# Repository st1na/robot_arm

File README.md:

# robot_arm
READ Doc.pdf for more info. Language Bulgarian.

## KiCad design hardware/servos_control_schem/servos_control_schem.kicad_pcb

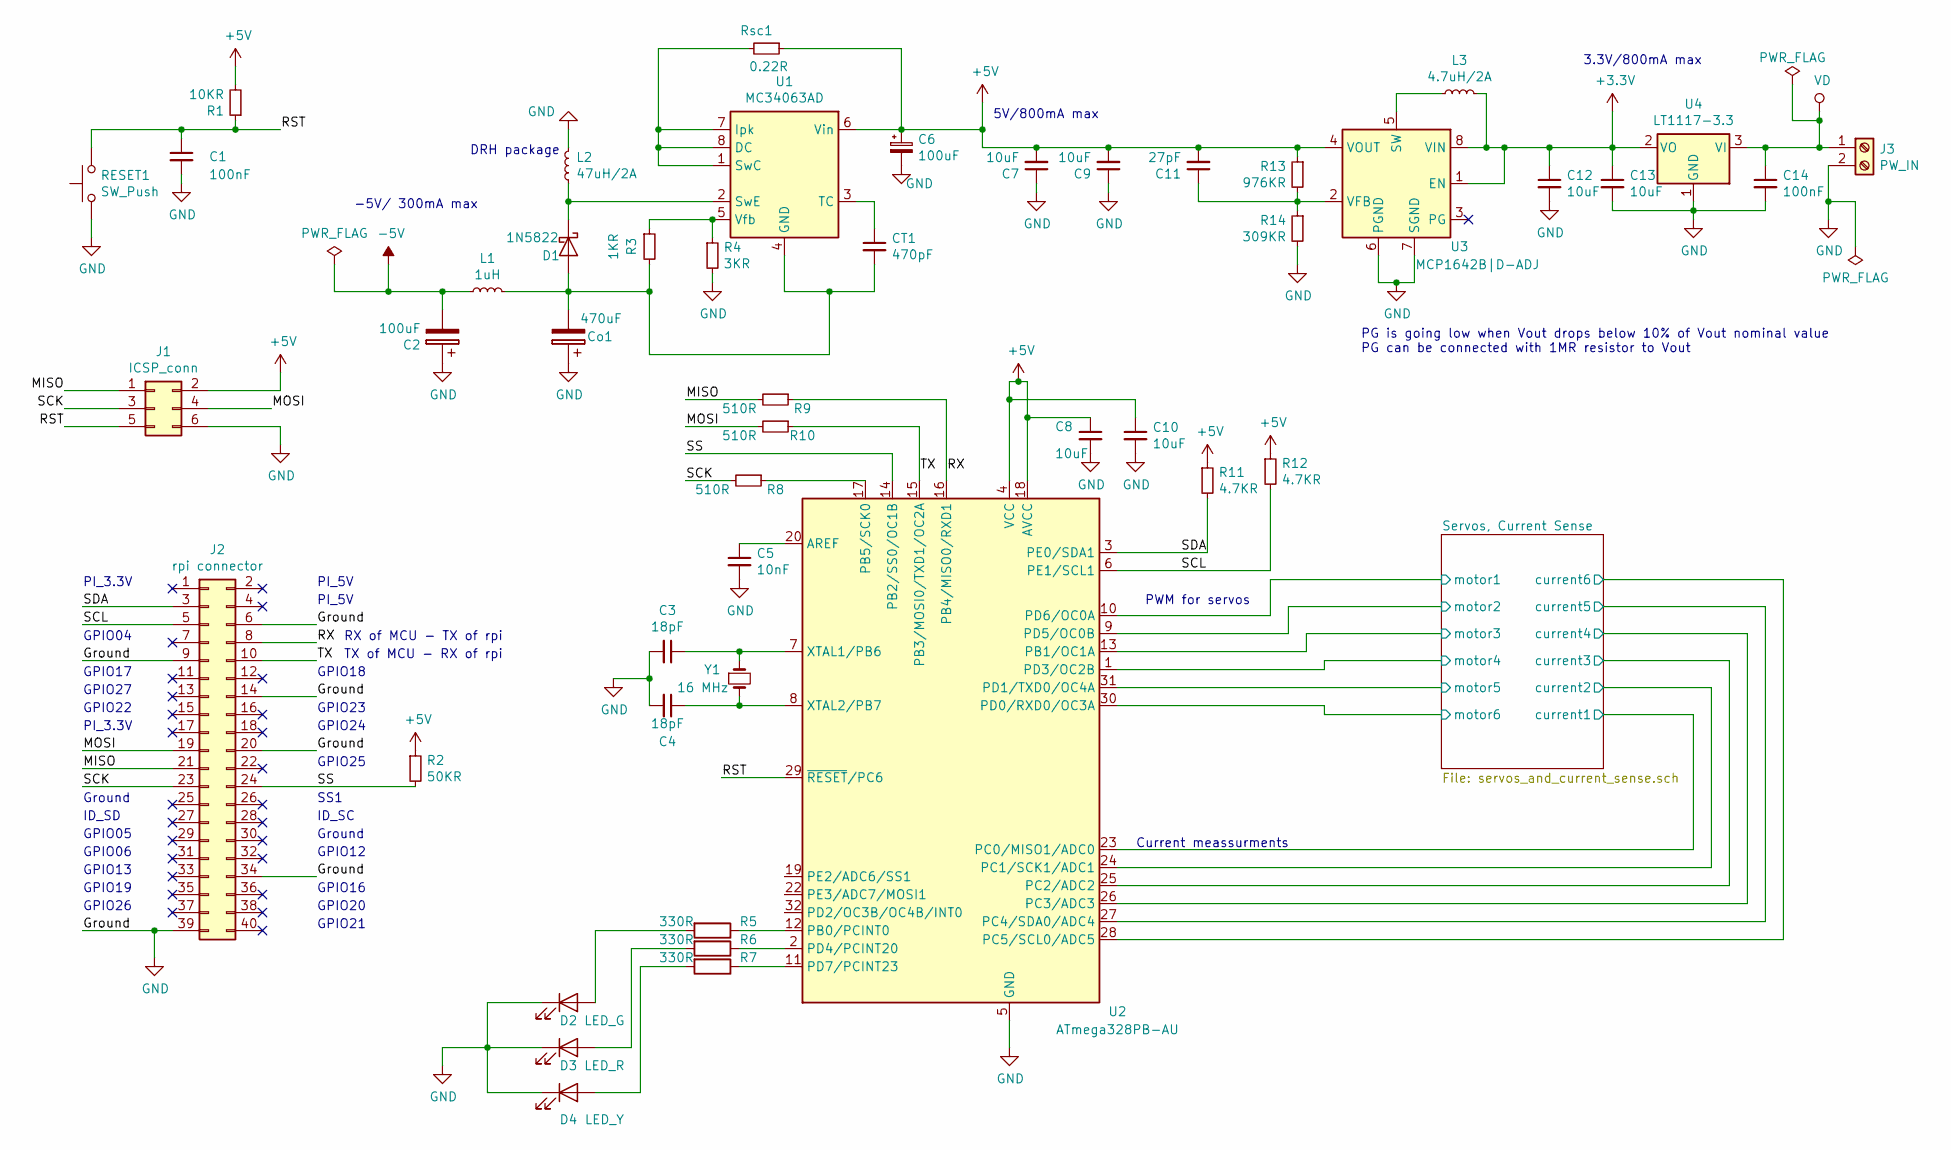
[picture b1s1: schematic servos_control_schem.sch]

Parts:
C1, C14: 100nF; C_0805_2012Metric_Pad1.15x1.40mm_HandSolder
C2, C6: 100uF; CP_Elec_6.3x5.4
C3, C4: 18pF; C_0805_2012Metric_Pad1.15x1.40mm_HandSolder
C5: 10nF; C_0805_2012Metric_Pad1.15x1.40mm_HandSolder
C7, C8, C9, C10, C12, C13: 10uF; C_0805_2012Metric_Pad1.15x1.40mm_HandSolder
C11: 27pF; C_0805_2012Metric_Pad1.15x1.40mm_HandSolder
CT1: 470pF; C_0805_2012Metric_Pad1.15x1.40mm_HandSolder
Co1: 470uF; CP_Elec_6.3x7.7
D1: 1N5822; D_SMC
D2: LED_G; LED_1206_3216Metric_Pad1.42x1.75mm_HandSolder
D3: LED_R; LED_1206_3216Metric_Pad1.42x1.75mm_HandSolder
D4: LED_Y; LED_1206_3216Metric_Pad1.42x1.75mm_HandSolder
J1: ICSP_conn; IDC-Header_2x03_P2.54mm_Vertical
J2: rpi connector; IDC-Header_2x20_P2.54mm_Vertical
J3: PW_IN; TerminalBlock_bornier-2_P5.08mm
L1: 1uH; L_1210_3225Metric_Pad1.42x2.65mm_HandSolder
L2: 47uH/2A; L_12x12mm_H6mm
L3: 4.7uH/2A; L_7.3x7.3_H3.5
R1: 10KR; R_0805_2012Metric_Pad1.15x1.40mm_HandSolder
R2: 50KR; R_0805_2012Metric_Pad1.15x1.40mm_HandSolder
R3: 1KR; R_0805_2012Metric_Pad1.15x1.40mm_HandSolder
R4: 3KR; R_0805_2012Metric_Pad1.15x1.40mm_HandSolder
R5, R6, R7: 330R; R_0805_2012Metric_Pad1.15x1.40mm_HandSolder
R8, R9, R10: 510R; R_0805_2012Metric_Pad1.15x1.40mm_HandSolder
R11, R12: 4.7KR; R_0805_2012Metric_Pad1.15x1.40mm_HandSolder
R13: 976KR; R_0805_2012Metric_Pad1.15x1.40mm_HandSolder
R14: 309KR; R_0805_2012Metric_Pad1.15x1.40mm_HandSolder
RESET1: SW_Push; SW_SPST_FSMSM
Rsc1: 0.22R; R_0805_2012Metric_Pad1.15x1.40mm_HandSolder
U1: MC34063AD; SOIC-8_3.9x4.9mm_P1.27mm
U2: ATmega328PB-AU; TQFP-32_7x7mm_P0.8mm
U3: MCP1642B|D-ADJ; MSOP-8_3x3mm_P0.65mm
U4: LT1117-3.3; SOT-223
Y1: 16 MHz; Crystal_SMD_HC49-SD

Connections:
+3V3: C12.1, C13.1, L3.1, U3.1 (EN), U3.8 (VIN), U4.2 (VO)
+5V: C6.1, C7.2, C8.1, C9.2, C10.1, C11.2, J1.2, R1.2, R2.1, R11.1, R12.1, R13.1, Rsc1.1, U1.6 (Vin), U2.4 (VCC), U2.18 (AVCC), U3.4 (VOUT); also elsewhere on the board
-5V: C2.2, L1.1; also elsewhere on the board
/MISO: J1.1, J2.21, R9.2
/MOSI: J1.4, J2.19, R10.2
/RST: C1.1, J1.5, R1.1, RESET1.2, U2.29 (~RESET~/PC6)
/RX: J2.8, R9.1, U2.16 (PB4/MISO0/RXD1)
/SCK: J1.3, J2.23, R8.2
/SCL: J2.5, R12.2, U2.6 (PE1/SCL1)
/SDA: J2.3, R11.2, U2.3 (PE0/SDA1)
/SS: J2.24, R2.2, U2.14 (PB2/SS0/OC1B)
/Servos, Current Sense/current1: U2.23 (PC0/MISO1/ADC0); also elsewhere on the board
/Servos, Current Sense/current2: U2.24 (PC1/SCK1/ADC1); also elsewhere on the board
/Servos, Current Sense/current3: U2.25 (PC2/ADC2); also elsewhere on the board
/Servos, Current Sense/current4: U2.26 (PC3/ADC3); also elsewhere on the board
/Servos, Current Sense/current5: U2.27 (PC4/SDA0/ADC4); also elsewhere on the board
/Servos, Current Sense/current6: U2.28 (PC5/SCL0/ADC5); also elsewhere on the board
/Servos, Current Sense/motor1: U2.10 (PD6/OC0A); also elsewhere on the board
/Servos, Current Sense/motor2: U2.9 (PD5/OC0B); also elsewhere on the board
/Servos, Current Sense/motor3: U2.13 (PB1/OC1A); also elsewhere on the board
/Servos, Current Sense/motor4: U2.1 (PD3/OC2B); also elsewhere on the board
/Servos, Current Sense/motor5: U2.31 (PD1/TXD0/OC4A); also elsewhere on the board
/Servos, Current Sense/motor6: U2.30 (PD0/RXD0/OC3A); also elsewhere on the board
/TX: J2.10, R10.1, U2.15 (PB3/MOSI0/TXD1/OC2A)
GND: C1.2, C2.1, C3.2, C4.2, C5.2, C6.2, C7.1, C8.2, C9.1, C10.2, C12.2, C13.2, C14.2, Co1.1, D2.1 (K), D3.1 (K), D4.1 (K), J1.6, J2.6, J2.9, J2.14, J2.20, J2.34, J2.39, J3.2, L2.2, R4.2, R14.2, RESET1.1, U2.5 (GND), U2.21 (GND), U3.6 (PGND), U3.7 (SGND), U4.1 (GND); also elsewhere on the board
unnamed: C3.1, U2.7 (XTAL1/PB6), Y1.1
unnamed: C4.1, U2.8 (XTAL2/PB7), Y1.2
unnamed: C5.1, U2.20 (AREF)
unnamed: C11.1, R13.2, R14.1, U3.2 (VFB)
unnamed: CT1.1, U1.3 (TC)
unnamed: CT1.2, Co1.2, D1.2 (A), L1.2, R3.2, U1.4 (GND)
unnamed: D1.1 (K), L2.1, U1.2 (SwE)
unnamed: D2.2 (A), R5.2
unnamed: D3.2 (A), R6.2
unnamed: D4.2 (A), R7.2
unnamed: L3.2, U3.5 (SW)
unnamed: R3.1, R4.1, U1.5 (Vfb)
unnamed: R5.1, U2.12 (PB0/PCINT0)
unnamed: R6.1, U2.2 (PD4/PCINT20)
unnamed: R7.1, U2.11 (PD7/PCINT23)
unnamed: R8.1, U2.17 (PB5/SCK0)
unnamed: Rsc1.2, U1.1 (SwC), U1.7 (Ipk), U1.8 (DC)
VD: C14.1, J3.1, U4.3 (VI); also elsewhere on the board

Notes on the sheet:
PWM for servos
Current meassurments
5V/800mA max
3.3V/800mA max
RX of MCU - TX of rpi
TX of MCU - RX of rpi
PG is going low when Vout drops below 10% of Vout nominal value PG can be connected with 1MR resistor to Vout
-5V/ 300mA max
DRH package
PI_3.3V
GPIO04
GPIO17
GPIO27
GPIO22
Ground
ID_SD
GPIO05
GPIO06
GPIO13
GPIO19
GPIO26
PI_5V
GPIO18
GPIO23
GPIO24
GPIO25
SS1
ID_SC
GPIO12
GPIO16
GPIO20
GPIO21

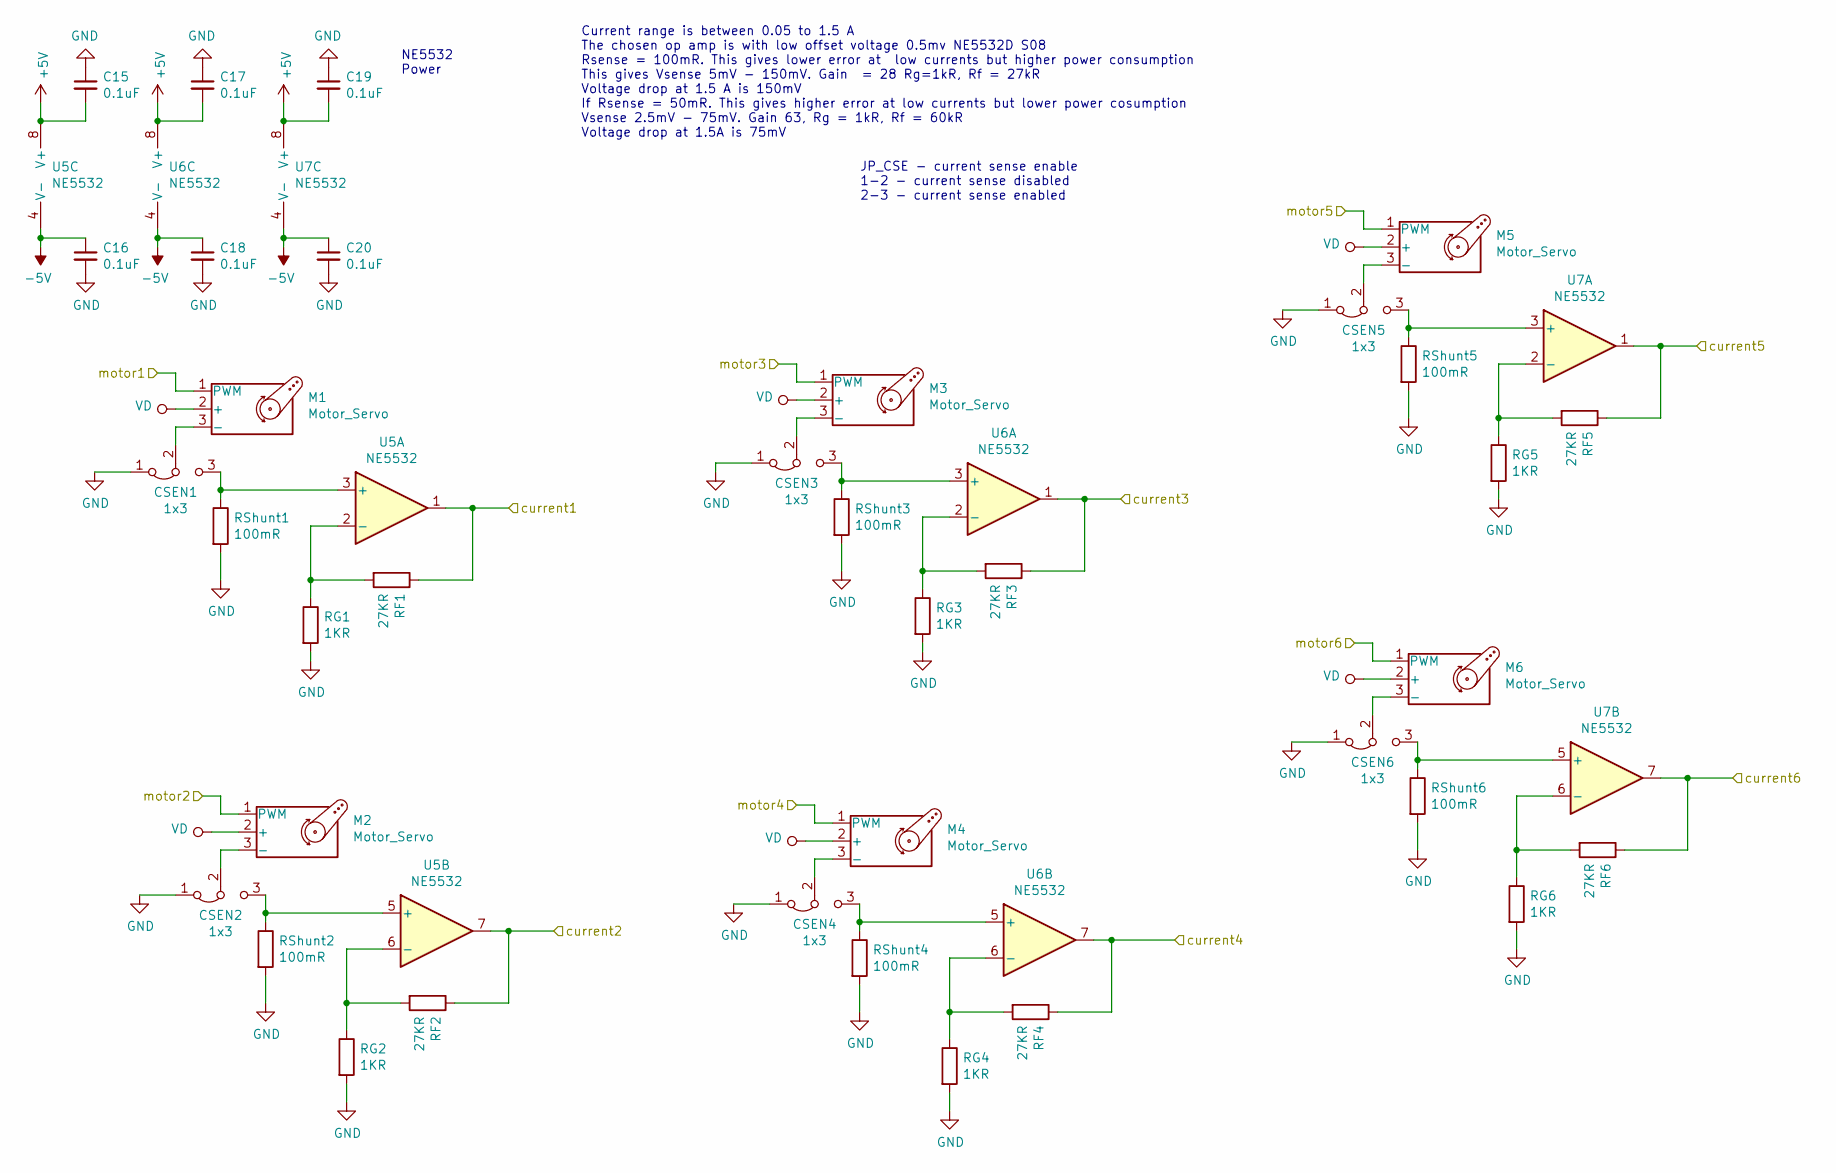
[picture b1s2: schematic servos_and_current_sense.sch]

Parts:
C15, C16, C17, C18, C19, C20: 0.1uF; C_0805_2012Metric_Pad1.15x1.40mm_HandSolder
CSEN1, CSEN2, CSEN3, CSEN4, CSEN5, CSEN6: 1x3; PinHeader_1x03_P2.54mm_Vertical
M1, M2, M3, M4, M5, M6: Motor_Servo; PinHeader_1x03_P2.54mm_Vertical
RF1, RF2, RF3, RF4, RF5, RF6: 27KR; R_0805_2012Metric_Pad1.15x1.40mm_HandSolder
RG1, RG2, RG3, RG4, RG5, RG6: 1KR; R_0805_2012Metric_Pad1.15x1.40mm_HandSolder
RShunt1, RShunt2, RShunt3, RShunt4, RShunt5, RShunt6: 100mR; R_2512_6332Metric_Pad1.52x3.35mm_HandSolder
U5, U6, U7: NE5532; SOIC-8_3.9x4.9mm_P1.27mm

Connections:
+5V: C15.2, C17.2, C19.2, U5.8 (V+), U6.8 (V+), U7.8 (V+); also elsewhere on the board
-5V: C16.1, C18.1, C20.1, U5.4 (V-), U6.4 (V-), U7.4 (V-); also elsewhere on the board
/Servos, Current Sense/current1: RF1.1, U5.1; also elsewhere on the board
/Servos, Current Sense/current2: RF2.1, U5.7; also elsewhere on the board
/Servos, Current Sense/current3: RF3.1, U6.1; also elsewhere on the board
/Servos, Current Sense/current4: RF4.1, U6.7; also elsewhere on the board
/Servos, Current Sense/current5: RF5.1, U7.1; also elsewhere on the board
/Servos, Current Sense/current6: RF6.1, U7.7; also elsewhere on the board
/Servos, Current Sense/motor1: M1.1 (PWM); also elsewhere on the board
/Servos, Current Sense/motor2: M2.1 (PWM); also elsewhere on the board
/Servos, Current Sense/motor3: M3.1 (PWM); also elsewhere on the board
/Servos, Current Sense/motor4: M4.1 (PWM); also elsewhere on the board
/Servos, Current Sense/motor5: M5.1 (PWM); also elsewhere on the board
/Servos, Current Sense/motor6: M6.1 (PWM); also elsewhere on the board
GND: C15.1, C16.2, C17.1, C18.2, C19.1, C20.2, CSEN1.1 (A), CSEN2.1 (A), CSEN3.1 (A), CSEN4.1 (A), CSEN5.1 (A), CSEN6.1 (A), RG1.2, RG2.2, RG3.2, RG4.2, RG5.2, RG6.2, RShunt1.2, RShunt2.2, RShunt3.2, RShunt4.2, RShunt5.2, RShunt6.2; also elsewhere on the board
unnamed: CSEN1.2 (C), M1.3 (-)
unnamed: CSEN1.3 (B), RShunt1.1, U5.3 (+)
unnamed: CSEN2.2 (C), M2.3 (-)
unnamed: CSEN2.3 (B), RShunt2.1, U5.5 (+)
unnamed: CSEN3.2 (C), M3.3 (-)
unnamed: CSEN3.3 (B), RShunt3.1, U6.3 (+)
unnamed: CSEN4.2 (C), M4.3 (-)
unnamed: CSEN4.3 (B), RShunt4.1, U6.5 (+)
unnamed: CSEN5.2 (C), M5.3 (-)
unnamed: CSEN5.3 (B), RShunt5.1, U7.3 (+)
unnamed: CSEN6.2 (C), M6.3 (-)
unnamed: CSEN6.3 (B), RShunt6.1, U7.5 (+)
unnamed: RF1.2, RG1.1, U5.2 (-)
unnamed: RF2.2, RG2.1, U5.6 (-)
unnamed: RF3.2, RG3.1, U6.2 (-)
unnamed: RF4.2, RG4.1, U6.6 (-)
unnamed: RF5.2, RG5.1, U7.2 (-)
unnamed: RF6.2, RG6.1, U7.6 (-)
VD: M1.2 (+), M2.2 (+), M3.2 (+), M4.2 (+), M5.2 (+), M6.2 (+); also elsewhere on the board

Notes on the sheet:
NE5532 Power
Current range is between 0.05 to 1.5 A The chosen op amp is with low offset voltage 0.5mv NE5532D S08 Rsense = 100mR. This gives lower error at low currents but higher power consumption This gives Vsense 5mV - 150mV. Gain = 28 Rg=1kR, Rf = 27kR Voltage drop at 1.5 A is 150mV If Rsense = 50mR. This 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
JP_CSE - current sense enable 1-2 - current sense disabled 2-3 - current sense enabled

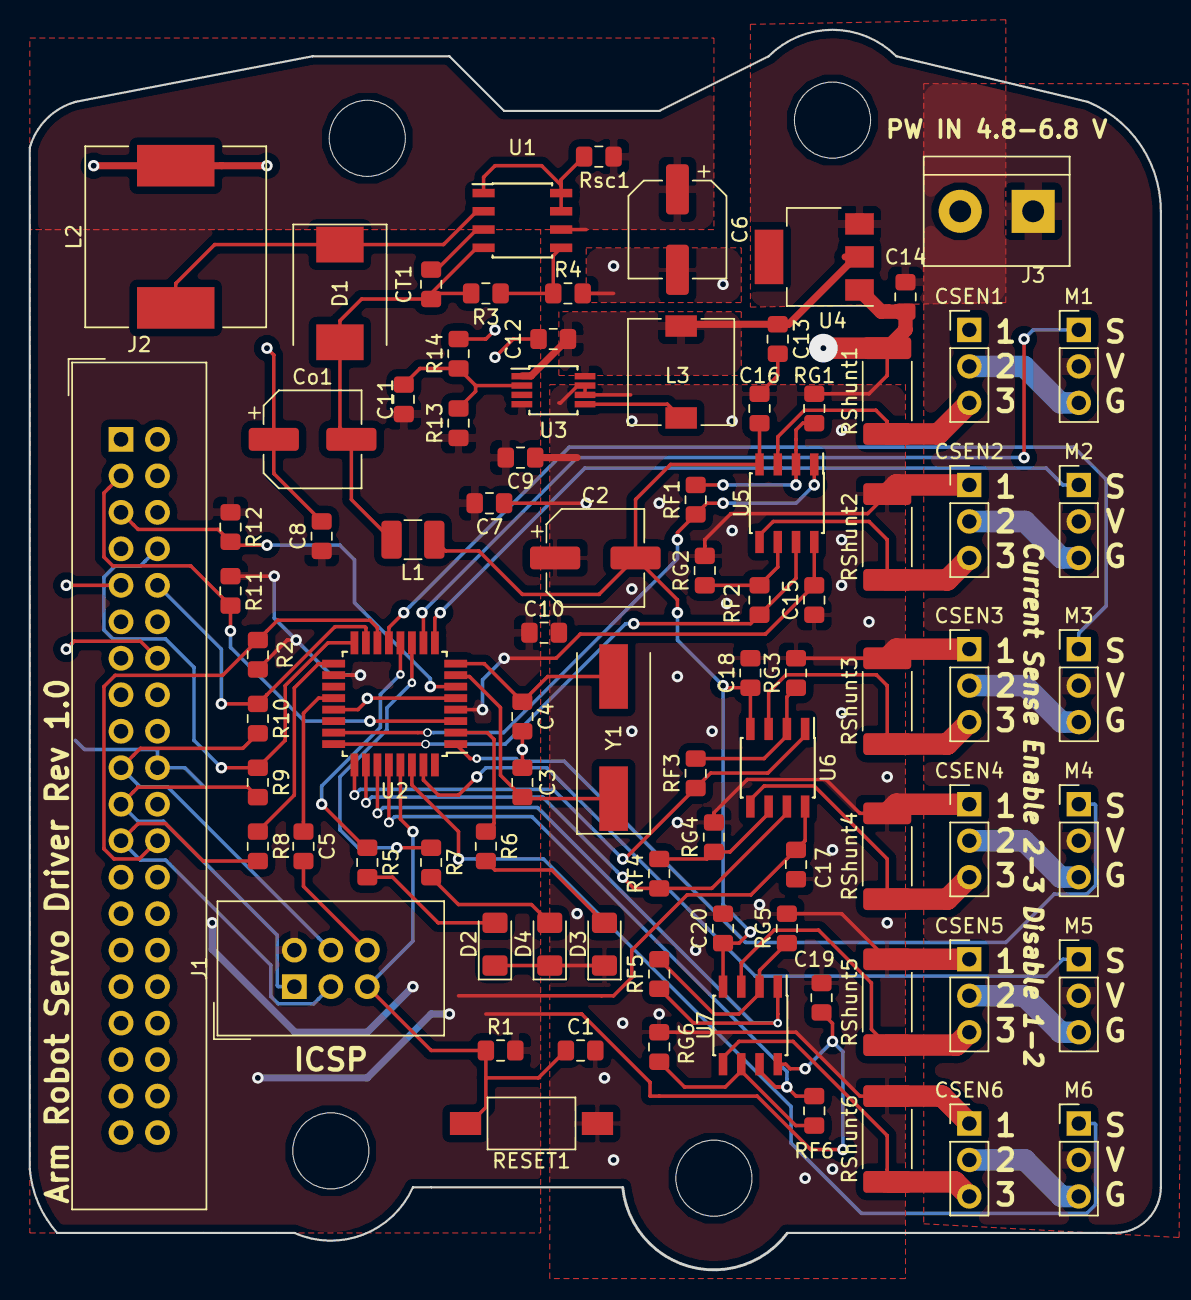
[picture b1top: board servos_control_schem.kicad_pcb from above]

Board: 2 copper layers, 78.7 x 86.3 mm, 86 parts (0 on the bottom side), 61 nets.

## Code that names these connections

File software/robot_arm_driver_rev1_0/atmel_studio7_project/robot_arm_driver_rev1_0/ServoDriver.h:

/*
 * ServoDriver.h
 *
 * Created: 06/04/2019 17:50:24
 *  Author: st1na
 */ 


#ifndef SERVODRIVER_H_
#define SERVODRIVER_H_

#define F_CPU 16000000
#define __DELAY_BACKWARD_COMPATIBLE__

#include <avr/io.h>
#include <stdbool.h>
#include <avr/interrupt.h>
#include <stdint.h>
#include <util/delay.h>


#define DDR_MOTOR DDRD
#define DDR_MOTOR3 DDRB
#define PORT_MOTOR PORTD
#define MOTOR1 PD6
#define MOTOR2 PD5
#define MOTOR3 PB1
#define MOTOR4 PD3
#define MOTOR5 PD1
#define MOTOR6 PD0

#define NUM_JOINTS		6
#define ARM_JOINTS		5
#define GRIPPER_JOINT	6

volatile double servo1_us;
volatile double servo2_us;
volatile double servo4_us;
#define servo3_us OCR1A
#define servo5_us OCR4A
#define servo6_us OCR3A

typedef struct delay{
	volatile double min_delay ;
	volatile double mid_delay ;
	volatile double max_delay ;
	volatile uint8_t min_delay_motor;
	volatile uint8_t mid_delay_motor;
	volatile uint8_t max_delay_motor;
		
} delay ;

delay servo_delay;

void delay_determine();
void initPWM();
void softwarePWMServo(double motor1_us, double motor2_us, double motor4_us);
void setServoAngles(uint8_t* angles);
void anglesToMiliSec(uint8_t* angles, uint16_t* angles_ms);

#endif /* SERVODRIVER_H_ */

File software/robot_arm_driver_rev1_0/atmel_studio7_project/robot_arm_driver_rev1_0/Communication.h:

/*
 * Communication.h
 *
 * Created: 05/04/2019 14:09:56
 *  Author: st1na
 */ 


#ifndef COMMUNICATION_H_
#define COMMUNICATION_H_

// ----------------- Includes ----------------
#include <avr/io.h>
#include <stdbool.h>
#include <avr/interrupt.h>
#include <stdint.h>

// ----------------- Defines ------------------
#define LAST_JOINT_SEND 100
#define NUM_JOINTS		6
#define ARM_JOINTS		5
#define GRIPPER_JOINT	6

#define DDR_SPI DDRB
#define MISO PB4
#define MOSI PB3
#define SS	PB2
#define SCK PB5

// Received joint are in range [-90,+90]
// Last byte hold END_OF_TRANSMISSION 
volatile int8_t joints_buffer[7];
// Mapped joints to [0; 180] 
volatile uint8_t u_joints_buffer[6];
volatile uint8_t joint_number;
volatile bool process_joints;

// ----------------- Prototypes -----------------

void initSPISlave(void);
void mapJointsFromSPI(void);
bool checkSPI_status(void);
void getJointsFromSPI(uint8_t*);
void clearSPI(void);

#endif /* COMMUNICATION_H_ */

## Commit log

2019-04-23 URDF simple example
2019-04-29 ROS packages tarball
2019-04-29 fi_kine add
2019-04-29 ROS packages zip
2019-04-29 Simulation launch
2019-04-29 get_input.py change
2019-05-04 SPI enable
2019-05-04 Allow exution = true
2019-05-04 Bash starting scripts
